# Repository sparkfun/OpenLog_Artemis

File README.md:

SparkFun OpenLog Artemis
===========================================================

<table class="table table-hover table-striped table-bordered">
  <tr align="center">
   <td></td>
   <td></td>
  </tr>
  <tr align="center">
    <td><a href="https://www.sparkfun.com/products/16832">SparkFun OpenLog Artemis (DEV-16832)</a></td>
    <td><a href="https://www.sparkfun.com/products/15846">SparkX OpenLog Artemis (SPX-15846)</a></td>
  </tr>
</table>

The OpenLog Artemis is an open source datalogger that comes preprogrammed to automatically log IMU, GPS, serial data, and various pressure, humidity, and distance sensors. All without writing a single line of code! OLA automatically detects, configures, and logs Qwiic sensors. OLA is designed for users who just need to capture a bunch of data to a CSV and get back to their larger project.

Included on every OpenLog Artemis is an IMU for built-in logging of triple axis accelerometer, gyro, and magnetometer. Whereas the original [9DOF Razor](https://www.sparkfun.com/products/14001) used the old MPU-9250, the OpenLog Artemis uses the latest [ICM-20948](https://www.sparkfun.com/products/15335) capable of nearly 1kHz logging of all 9 axis. We then took over a decade of experience with the original [OpenLog](https://www.sparkfun.com/products/13712) and took it much farther. Simply power up OpenLog Artemis and all incoming serial data is automatically recorded to a log file. Baud rates up to 921600bps are supported! Additionally, based on feedback from users we've added an onboard RTC so that all data can be time stamped.

OpenLog Artemis is highly configurable over an easy to use serial interface. Simply plug in a USB C cable and open a terminal at 115200kbps. The logging output is automatically streamed to both the terminal and the microSD. Pressing any key will open the configuration menu.

The OpenLog Artemis automatically scans, detects, configures, and logs various Qwiic sensors plugged into the board (no soldering required!). Currently, auto-detection is supported on the following Qwiic products:

* Any u-blox GPS Modules (Lat/Long, Altitude, Velocity, SIV, Time, Date) such as:
  * [ZED-F9P](https://www.sparkfun.com/products/15136) 1cm High Precision GPS
  * [NEO-M8P-2](https://www.sparkfun.com/products/15005) 2.5cm High Precision GPS
  * [SAM-M8Q](https://www.sparkfun.com/products/15210) 1.5m 72 Channel GPS
  * [ZOE-M8Q](https://www.sparkfun.com/products/15193) 1.5m Compact GPS
  * [NEO-M9N](https://www.sparkfun.com/products/15712) 1.5m GPS
  * [MAX-M10S](https://www.sparkfun.com/products/18037) 1.5m Ultra-Low Power GPS
* [MCP9600 Thermocouple Amplifier](https://www.sparkfun.com/products/16294)
* [NAU7802 Load Cell Amplifier](https://www.sparkfun.com/products/15242)
* [LPS25HB Barometric Pressure Sensor](https://www.sparkfun.com/products/14767)
* [BME280 Humidity and Barometric Pressure Sensor](https://www.sparkfun.com/products/15440)
* [MS5637 Barometric Pressure Sensor](https://www.sparkfun.com/products/14688)
* [MS5837 Depth / Pressure Sensor](https://www.sparkfun.com/products/17709)
* [SDP3X Differential Pressure Sensor](https://www.sparkfun.com/products/17874)
* [MS8607 Pressure Humidity Temperature Sensor](https://www.sparkfun.com/products/16298)
* [MPR0025PA MicroPressure Sensor](https://www.sparkfun.com/products/16476)
* [TMP102 Temperature Sensor] (https://www.sparkfun.com/products/13314)
* [TMP117 High Precision Temperature Sensor](https://www.sparkfun.com/products/15805)
* [AHT20 Humidity and Temperature Sensor](https://www.sparkfun.com/products/16618)
* [SHTC3 Humidity and Temperature Sensor](https://www.sparkfun.com/products/16467)
* [CCS811 Air Quality Sensor](https://www.sparkfun.com/products/14348)
* [SGP30 Air Quality Sensor](https://www.sparkfun.com/products/16531)
* [SGP40 Air Quality Sensor](https://www.sparkfun.com/products/17729)
* [SCD30 CO<sub>2</sub> and Air Quality Sensor](https://www.sparkfun.com/products/15112)
* [SN-GCJA5 Particle Sensor](https://www.sparkfun.com/products/17123)
* [VEML6075 UV Sensor](https://www.sparkfun.com/products/15089)
* [VCNL4040 Proximity Sensor](https://www.sparkfun.com/products/15177)
* [VL53L1X LIDAR Distance Sensor](https://www.sparkfun.com/products/14722)
* [ADS122C04 ADC PT100 Sensor](https://www.sparkfun.com/products/16770)
* [Qwiic Mux](https://www.sparkfun.com/products/16784) allowing for the chaining of up to 64 unique buses!
* [Pulse Oximeter and Heart Rate Sensor](https://www.sparkfun.com/products/15219) (requires exclusive use of pins 32 and 11)
* [ISM330DHCX IMU](https://www.sparkfun.com/products/19764)
* [MMC5983MA Magnetometer](https://www.sparkfun.com/products/19921)
* [KX134 Accelerometer](https://www.sparkfun.com/products/17589)
* [ADS1015 ADC](https://www.sparkfun.com/products/15334)
* [LPS28DFW Barometer](https://www.sparkfun.com/products/21221)
* [VEML7700 Ambient Light Sensor](https://www.sparkfun.com/products/18981)
* [TMP102 Temperature Sensor](https://www.sparkfun.com/sparkfun-digital-temperature-sensor-tmp102-qwiic.html)

Very low power logging is supported. OpenLog Artemis can be configured to take readings at 500 times a second, or as slow as 1 reading every 24 hours. You choose! When there is more than 2 seconds between readings OLA will automatically power down itself and the sensors on the bus resulting in a sleep current of approximately 18uA. This means a normal [2Ah battery](https://www.sparkfun.com/products/13855) will enable logging for more than 4,000 days! OpenLog Artemis has built-in LiPo charging set at 450mA/hr.

New features are constantly being added so we’ve released an easy to use firmware upgrade tool. No need to install Arduino or a bunch of libraries, simply open the [Artemis Firmware Upload GUI](https://github.com/sparkfun/Artemis-Firmware-Upload-GUI), load the latest OLA firmware, and add features to OpenLog Artemis as they come out! Full instructions are available in [UPGRADE.md](UPGRADE.md).

The OLA can be tailored to many different applications and we will be releasing custom versions of the firmware for those too:

* [Latest OLA firmware](https://github.com/sparkfun/OpenLog_Artemis/tree/main/Binaries)
* [Geophone Logger firmware](https://github.com/sparkfun/OpenLog_Artemis_Geophone_Logger) for logging seismic activity
* [GNSS Logger](https://github.com/sparkfun/OpenLog_Artemis_GNSS_Logger) for advanced data logging with the u-blox F9 and M9 GNSS modules including support for RAWX and RELPOSNED

Repository Contents
-------------------

* **/Binaries** - The binary files for the different versions of the OLA firmware.
* **/Firmware** - The main sketch that runs OpenLog Artemis as well as a variety of sketches to test various sensor interfaces and power saving states.
* **/Hardware** - Eagle files.

Documentation
--------------

* **[Hookup Guide](https://learn.sparkfun.com/tutorials/openlog-artemis-hookup-guide)** - hookup guide for the OLA.
* **[UPGRADE.md](./UPGRADE.md)** - contains full instructions on how to upgrade the firmware on the OLA using the [Artemis Firmware Upload GUI](https://github.com/sparkfun/Artemis-Firmware-Upload-GUI).
* **[CONTRIBUTING.md](./CONTRIBUTING.md)** - guidance on how to contribute to this library.
* **[Installing an Arduino Library Guide](https://learn.sparkfun.com/tutorials/installing-an-arduino-library)** - OLA includes a large number of libraries that will need to be installed before compiling will work.
* **[ADDING_SENSORS.md](./ADDING_SENSORS.md)** - contains _abbreviated_ instructions on how to add a new sensor to the OLA firmware. It's more of an aide-memoire really... Sorry about that.
* **[COMPILE_BINARY.md](./COMPILE_BINARY.md)** - contains instructions on how to compile the OLA firmware binary manually using Docker.
* **[SENSOR_UNITS.md](./SENSOR_UNITS.md)** - contains a summary of the units used for each sensor measurement.

Product Versions
----------------
* [DEV-19426](https://www.sparkfun.com/products/19426) - SparkFun OpenLog Artemis without IMU
* [DEV-16832](https://www.sparkfun.com/products/16832) - SparkFun OpenLog Artemis
* [SPX-15846](https://www.sparkfun.com/products/15846) - SparkX OpenLog Artemis

License Information
-------------------

This product is _**open source**_!

Various bits of the code have different licenses applied. Anything SparkFun wrote is beerware; if you see me (or any other SparkFun employee) at the local, and you've found our code helpful, please buy us a round!

Please use, reuse, and modify these files as you see fit. Please maintain attribution to SparkFun Electronics and release anything derivative under the same license.

Distributed as-is; no warranty is given.

- Your friends at SparkFun.

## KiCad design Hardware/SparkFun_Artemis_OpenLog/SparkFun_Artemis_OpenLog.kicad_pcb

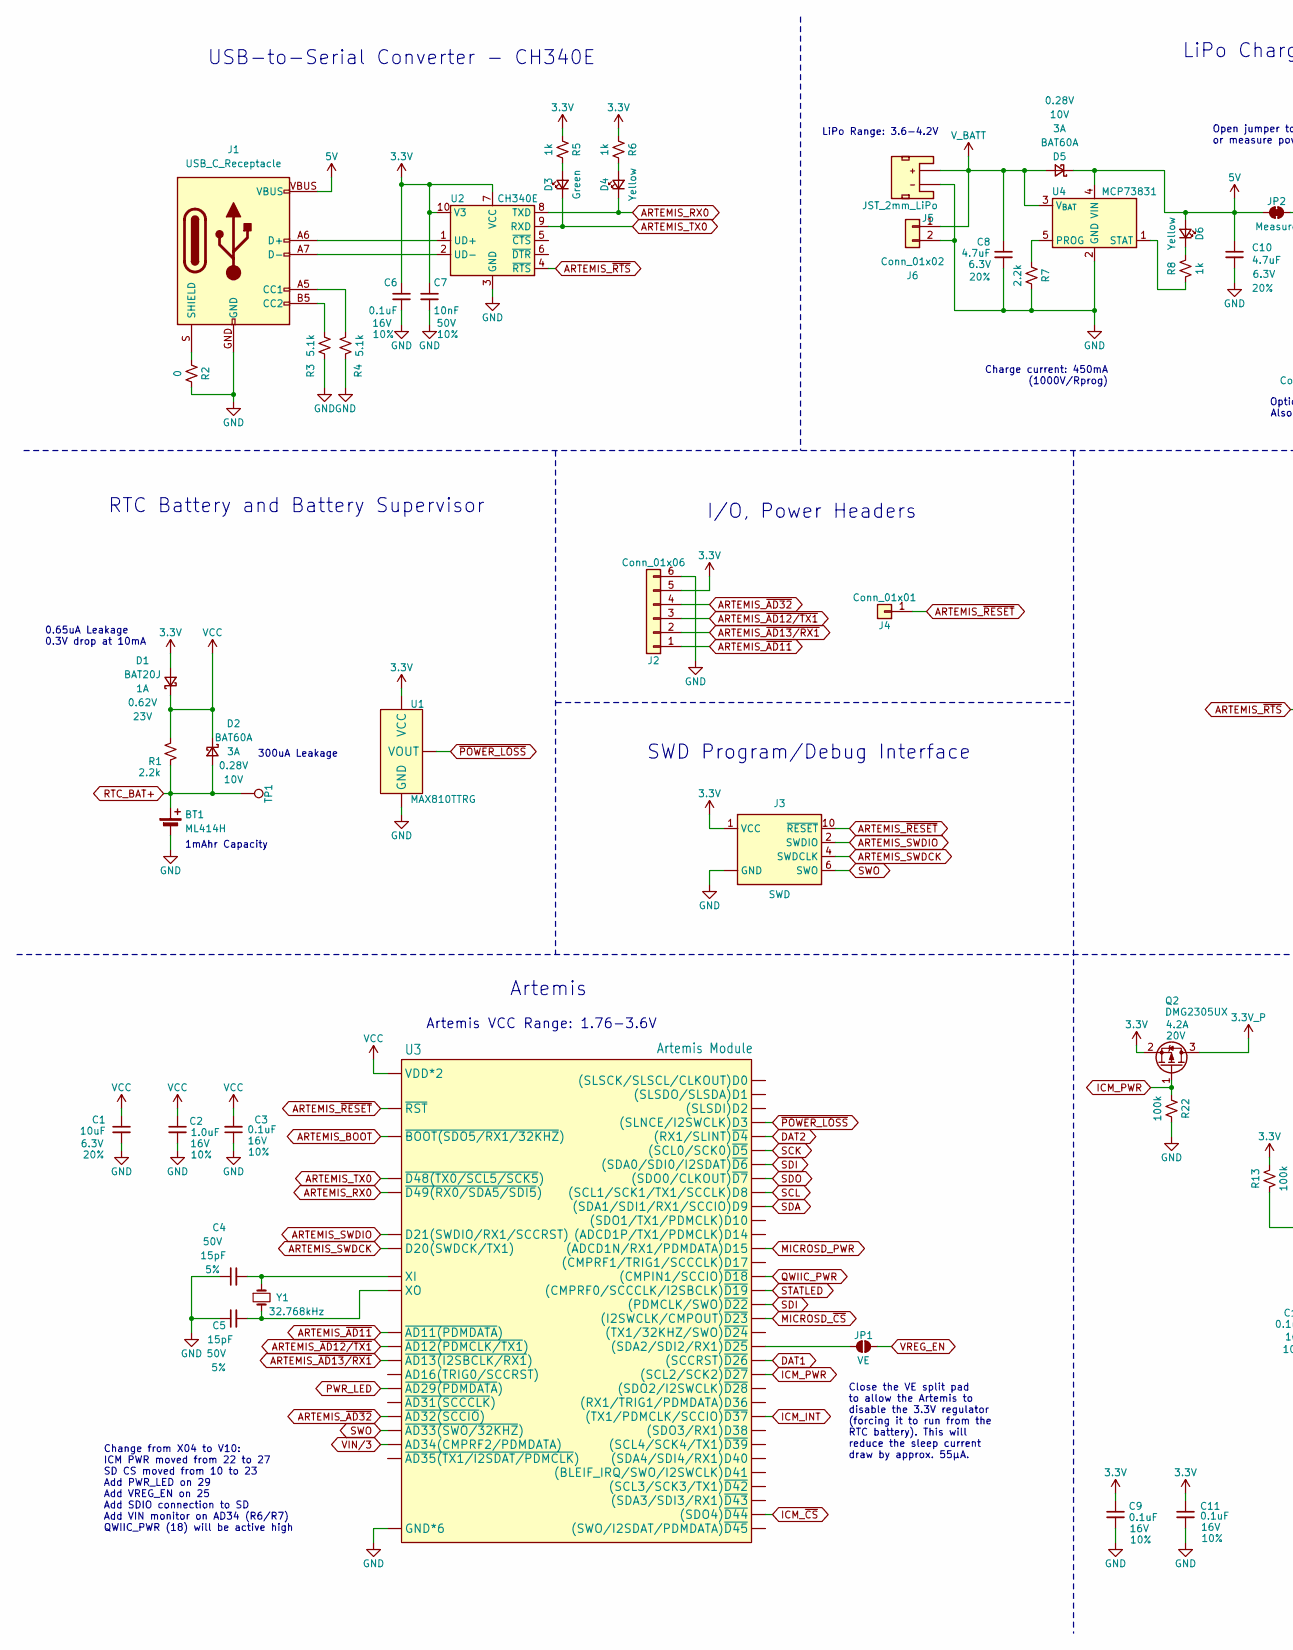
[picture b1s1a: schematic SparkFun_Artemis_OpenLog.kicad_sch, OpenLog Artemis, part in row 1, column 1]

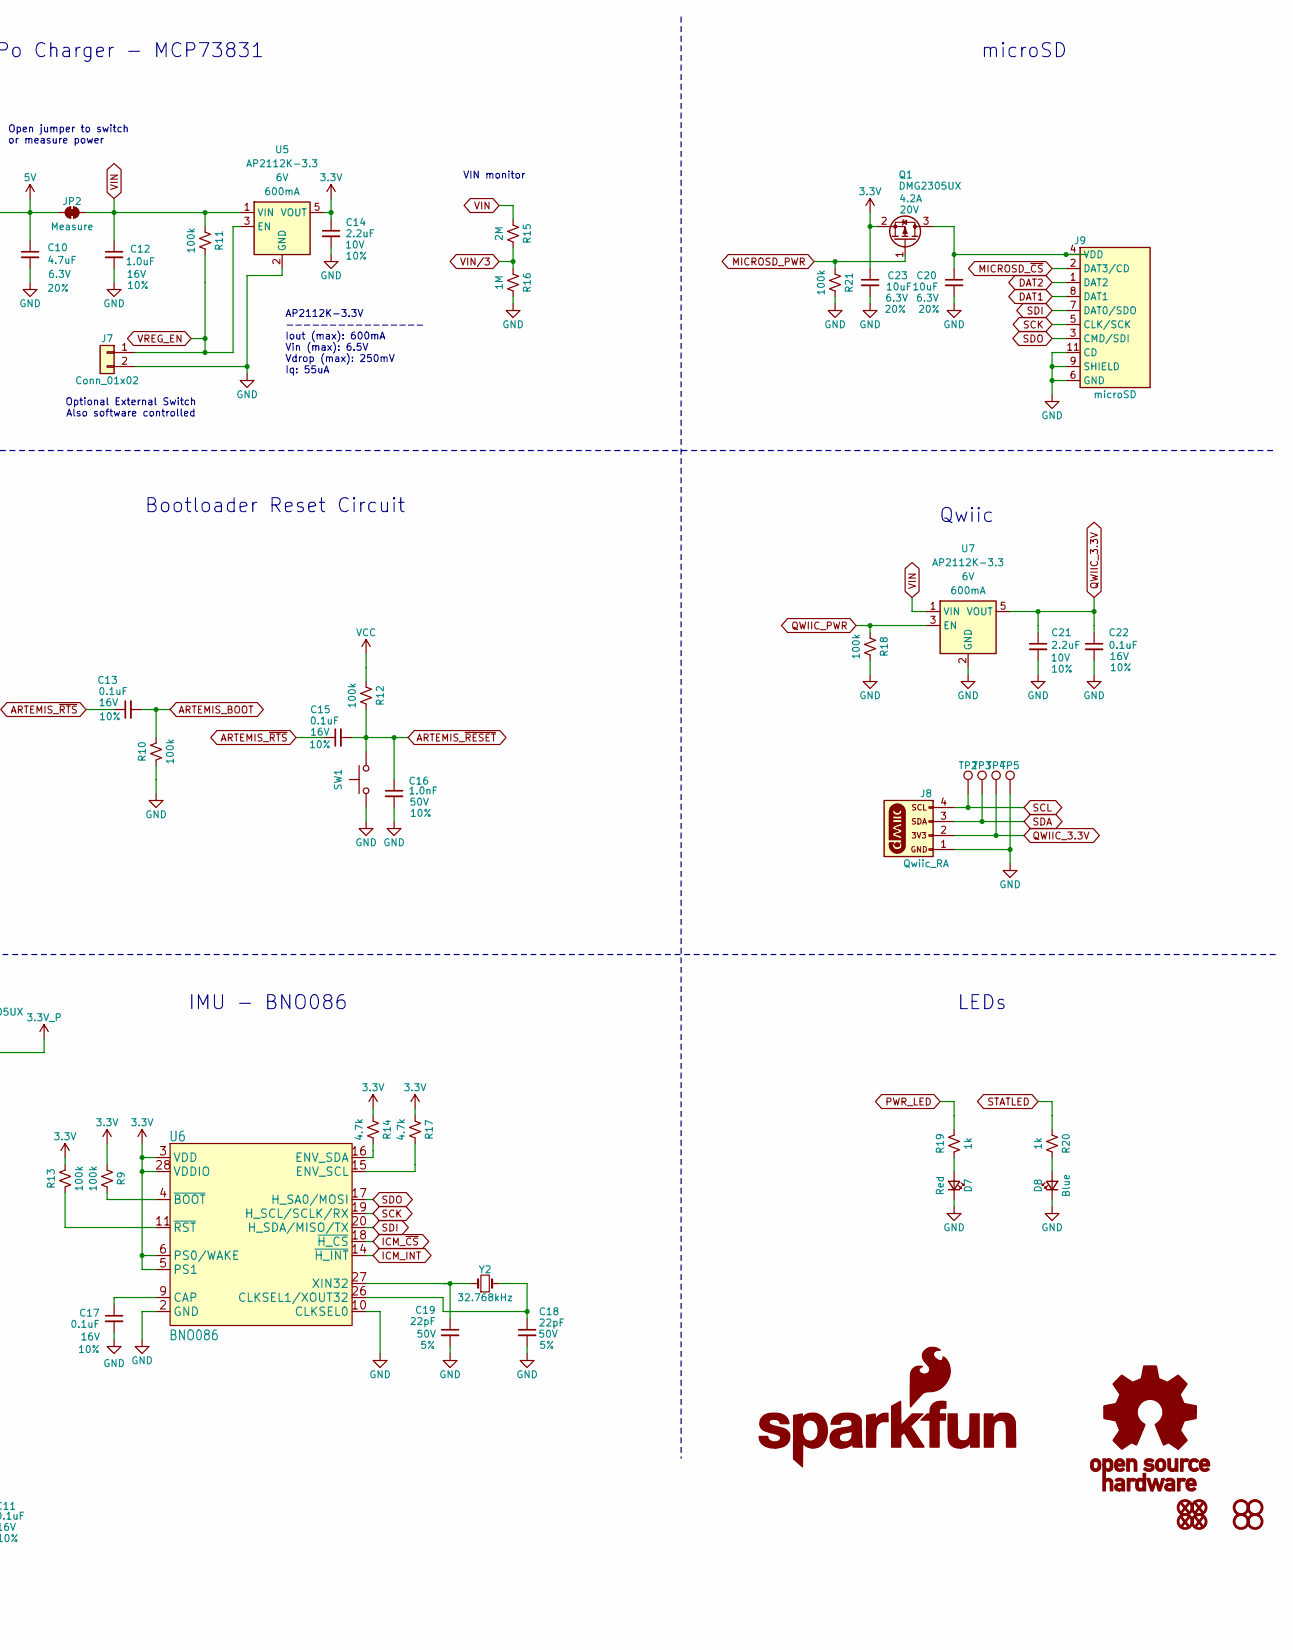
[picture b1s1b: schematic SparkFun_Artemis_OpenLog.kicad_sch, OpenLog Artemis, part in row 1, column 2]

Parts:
BT1: ML414H; ML414H_IV01E
C1, C20, C23: 10uF; C_0402_1005Metric; Voltage 6.3V; Tolerance 20%
C2, C12: 1.0uF; C_0402_1005Metric; Voltage 16V; Tolerance 10%
C3, C6, C9, C11, C13, C15, C17, C22: 0.1uF; C_0402_1005Metric; Voltage 16V; Tolerance 10%
C4, C5: 15pF; C_0402_1005Metric; Voltage 50V; Tolerance 5%
C7: 10nF; C_0402_1005Metric; Voltage 50V; Tolerance 10%
C8, C10: 4.7uF; C_0402_1005Metric; Voltage 6.3V; Tolerance 20%
C14, C21: 2.2uF; C_0402_1005Metric; Voltage 10V; Tolerance 10%
C16: 1.0nF; C_0402_1005Metric; Voltage 50V; Tolerance 10%
C18, C19: 22pF; C_0402_1005Metric; Voltage 50V; Tolerance 5%
D1: BAT20J; SOD-323
D2, D5: BAT60A; SOD-323
D3: Green; LED_0603_1608Metric_Green
D4, D6: Yellow; LED_0603_1608Metric_Yellow
D7: Red; LED_0603_1608Metric_Red
D8: Blue; LED_0603_1608Metric_Blue
FID1, FID2, FID3, FID4: Fiducial_0.5mm; Fiducial_0.5mm_Mask1mm
G1: SparkFun_Logo
G2: OSHW_Logo; Creative_Commons_License
J1: USB_C_Receptacle; USB-C_16
J2: Conn_01x06; 1x06_P2.54mm
J3: SWD; 2x05_P1.27mm
J4: Conn_01x01; 1x01_P2.54mm
J5: JST_2mm_LiPo; JST_1x02_P2.0mm_Horizontal_SMD
J6, J7: Conn_01x02; 1x02_P2.54mm
J8: Qwiic_RA; JST_1x04_P1.0mm_Horizontal_SMD
J9: microSD; microSD_SOCKET
JP1: VE; Jumper_2_NO
JP2: Measure; Jumper_2_PTH_SMD_Combo-NC
Q1, Q2: DMG2305UX; SOT23-3
R1, R7: 2.2k; R_0402_1005Metric
R2: 0; R_0402_1005Metric
R3, R4: 5.1k; R_0402_1005Metric
R5, R6, R8, R19, R20: 1k; R_0402_1005Metric
R9, R10, R11, R12, R13, R18, R21, R22: 100k; R_0402_1005Metric
R14, R17: 4.7k; R_0402_1005Metric
R15: 2M; R_0603_1608Metric
R16: 1M; R_0603_1608Metric
ST1, ST2, ST3, ST4: Standoff
SW1: SMD_4.6x2.8mm_h2.5mm; Push_SMD_4.6x2.8mm_h2.5mm
TP1: 1.0mm; TestPoint-1.0mm
TP2, TP3, TP4, TP5: 0.75mm; TestPoint-0.75mm
U1: MAX810TTRG; SOT23-3
U2: CH340E; MSOP-10_3x3mm_P0.5mm
U3: Artemis Module; Artemis_Module
U4: MCP73831; SOT23-5
U5, U7: AP2112K-3.3; SOT23-5
U6: BNO086; LGA-28_5.2x3.8mm_P0.5mm
Y1, Y2: 32.768kHz; Crystal_SMD_3.2x1.5mm

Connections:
3.3V: C6.1, C7.1, C9.1, C11.1, C14.1, C23.1, D1.2 (A), J2.5, J3.1 (VCC), Q1.2 (S), Q2.2 (S), R5.2, R6.2, R9.2, R13.2, R14.2, R17.2, U1.3 (VCC), U2.7 (VCC), U2.10 (V3), U5.5 (VOUT), U6.3 (VDD), U6.5 (PS1), U6.6 (PS0/WAKE), U6.28 (VDDIO)
5V: C10.1, D5.1 (K), D6.2 (A), J1.VBUS, JP2.1 (A), U4.4 (VIN)
ARTEMIS_BOOT: C13.2, R10.2, U3.BOOT (~BOOT(SDO5/RX1/32KHZ))
ARTEMIS_RX0: D4.1 (K), U2.8 (TXD), U3.RXI-0 (~D49(RX0/SDA5/SDI5))
ARTEMIS_SWDCK: J3.4 (SWDCLK), U3.SWDCK (D20(SWDCK/TX1))
ARTEMIS_SWDIO: J3.2 (SWDIO), U3.SWDIO (D21(SWDIO/RX1/SCCRST))
ARTEMIS_TX0: D3.1 (K), U2.9 (RXD), U3.TXO-0 (~D48(TX0/SCL5/SCK5))
ARTEMIS_~AD11: J2.1, U3.~AD11 (~AD11(PDMDATA))
ARTEMIS_~AD12/TX1: J2.3, U3.~AD12 (~AD12(PDMCLK/TX1))
ARTEMIS_~AD13/RX1: J2.2, U3.~AD13 (~AD13(I2SBCLK/RX1))
ARTEMIS_~AD32: J2.4, U3.~AD32 (~AD32(SCCIO))
ARTEMIS_~RESET: C15.2, C16.1, J3.10 (~RESET), J4.1 (Pin_1_1), R12.1, SW1.2, U3.~RST (~RST)
ARTEMIS_~RTS: C13.1, C15.1, U2.4 (~RTS)
DAT1: J9.8 (DAT1), U3.~D26 ((SCCRST)~D26)
DAT2: J9.1 (DAT2), U3.~D4 ((RX1/SLINT)~D4)
GND: BT1.-, C1.2, C2.2, C3.1, C4.1, C5.1, C6.2, C7.2, C8.2, C9.2, C10.2, C11.2, C12.2, C14.2, C16.2, C17.2, C18.2, C19.2, C20.2, C21.2, C22.2, C23.2, D7.1 (K), D8.1 (K), J1.GND, J2.6, J3.3 (GND), J3.5 (GND), J3.9 (GND), J5.1 (-), J6.2, J7.2, J8.1, J9.6 (GND), J9.9 (SHIELD), J9.10 (GND), J9.11 (CD), J9.12 (CD), R2.1, R3.1, R4.1, R7.1, R10.1, R16.1, R18.1, R21.1, R22.1, SW1.1, TP5.1 (1_1), U1.1 (GND), U2.3 (GND), U3.GND@1 (GND*6), U3.GND@22 (GND*6), U3.GND@38 (GND*6), U3.GND@39 (GND*6), U3.GND@47 (GND*6), U3.GND@59 (GND*6), U4.2 (GND), U5.2 (GND), U6.2 (GND), U6.10 (CLKSEL0), U6.25 (GNDIO), U7.2 (GND)
ICM_INT: U3.~D37 ((TX1/PDMCLK/SCCIO)~D37), U6.14 (~H_INT)
ICM_PWR: Q2.1 (G), R22.2, U3.~D27 ((SCL2/SCK2)~D27)
ICM_~CS: U3.~D44 ((SDO4)~D44), U6.18 (~H_CS)
MICROSD_PWR: Q1.1 (G), R21.2, U3.D15 ((ADCD1N/RX1/PDMDATA)D15)
MICROSD_~CS: J9.2 (DAT3/CD), U3.~D23 ((I2SWCLK/CMPOUT)~D23)
unnamed: C4.2, U3.XI, Y1.1
unnamed: C5.2, U3.XO, Y1.2
unnamed: D3.2 (A), R5.1
unnamed: D4.2 (A), R6.1
unnamed: D6.1 (K), R8.2
unnamed: D7.2 (A), R19.1
unnamed: D8.2 (A), R20.1
unnamed: J1.A5 (CC1), R4.2
unnamed: J1.B5 (CC2), R3.2
unnamed: J1.S (SHIELD), R2.2
unnamed: C20.1, J9.4 (VDD), Q1.3 (D)
unnamed: JP1.1 (A), U3.~D25 ((SDA2/SDI2/RX1)~D25)
unnamed: J1.A6 (D+), J1.B6 (D+), U2.1 (UD+)
unnamed: J1.A7 (D-), J1.B7 (D-), U2.2 (UD-)
unnamed: R7.2, U4.5 (PROG)
unnamed: R8.1, U4.1 (STAT)
unnamed: C17.1, U6.9 (CAP)
unnamed: R17.1, U6.15 (ENV_SCL)
unnamed: R14.1, U6.16 (ENV_SDA)
unnamed: R9.1, U6.4 (~BOOT)
PWR_LED: R19.2, U3.~AD29 (~AD29(PDMDATA))
QWIIC_3.3V: C21.1, C22.1, J8.2, TP4.1 (1_1), U7.5 (VOUT)
QWIIC_PWR: R18.2, U3.~D18 ((CMPIN1/SCCIO)~D18), U7.3 (EN)
RTC_BAT+: BT1.+, D2.2 (A), R1.1, TP1.1 (1_1)
SCK: J9.5 (CLK/SCK), U3.~D5 ((SCL0/SCK0)~D5), U6.19 (H_SCL/SCLK/RX)
SCL: J8.4, TP2.1 (1_1), U3.D8 ((SCL1/SCK1/TX1/SCCLK)D8)
SDA: J8.3, TP3.1 (1_1), U3.D9 ((SDA1/SDI1/RX1/SCCIO)D9)
SDI: J9.7 (DAT0/SDO), U3.~D6 ((SDA0/SDI0/I2SDAT)~D6), U3.~D22 ((PDMCLK/SWO)~D22), U6.20 (H_SDA/MISO/TX)
SDO: J9.3 (CMD/SDI), U3.D7 ((SDO0/CLKOUT)~D7), U6.17 (H_SA0/MOSI)
STATLED: R20.2, U3.~D19 ((CMPRF0/SCCCLK/I2SBCLK)~D19)
SWO: J3.6 (SWO), U3.~AD33/SWO (~AD33(SWO/32KHZ))
VCC: C1.1, C2.1, C3.2, D1.1 (K), D2.1 (K), R1.2, R12.2, U3.VDD@36 (VDD*2), U3.VDD@37 (VDD*2)
VIN: C12.1, JP2.2 (B), R11.2, R15.2, U5.1 (VIN), U7.1 (VIN)
VIN/3: R15.1, R16.2, U3.AD34 (AD34(CMPRF2/PDMDATA))
VREG_EN: J7.1, JP1.2 (B), R11.1, U5.3 (EN)
V_BATT: C8.1, D5.2 (A), J5.2 (+), J6.1, U4.3 (V_{BAT})
~POWER_LOSS: U1.2 (VOUT), U3.D3 ((SLNCE/I2SWCLK)D3)
~RST: R13.1, U6.11 (~RST)

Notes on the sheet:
Charge current: 450mA (1000V/Rprog)
LiPo Charger - MCP73831
USB-to-Serial Converter - CH340E
IMU - BNO086
300uA Leakage
0.65uA Leakage 0.3V drop at 10mA
Optional External Switch Also software controlled
Bootloader Reset Circuit
VIN monitor
RTC Battery and Battery Supervisor
1mAhr Capacity
Close the VE split pad to allow the Artemis to disable the 3.3V regulator (forcing it to run from the RTC battery). This will reduce the sleep current draw by approx. 55μA.
microSD
I/O, Power Headers
Change from X04 to V10: ICM PWR moved from 22 to 27 SD CS moved from 10 to 23 Add PWR_LED on 29 Add VREG_EN on 25 Add SDIO connection to SD Add VIN monitor on AD34 (R6/R7) QWIIC_PWR (18) will be active high
AP2112K-3.3V ---------------- Iout (max): 600mA Vin (max): 6.5V Vdrop (max): 250mV Iq: 55uA
Artemis
LiPo Range: 3.6-4.2V
SWD Program/Debug Interface
Qwiic
Open jumper to switch or measure power
LEDs
Artemis VCC Range: 1.76-3.6V

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
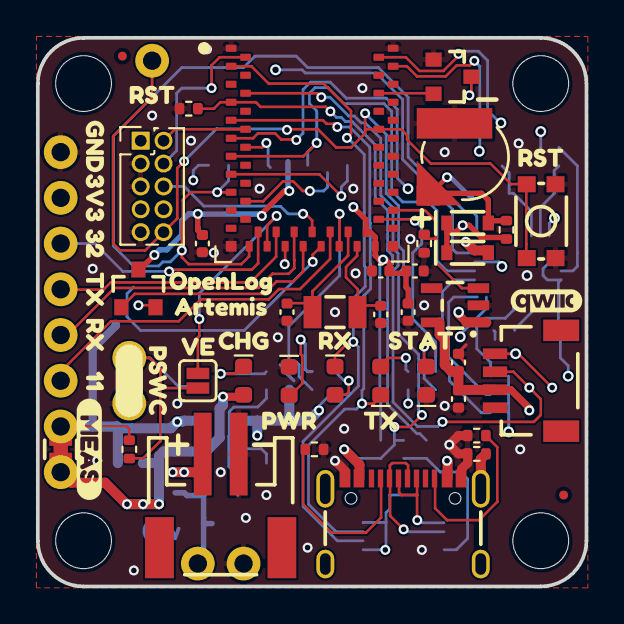
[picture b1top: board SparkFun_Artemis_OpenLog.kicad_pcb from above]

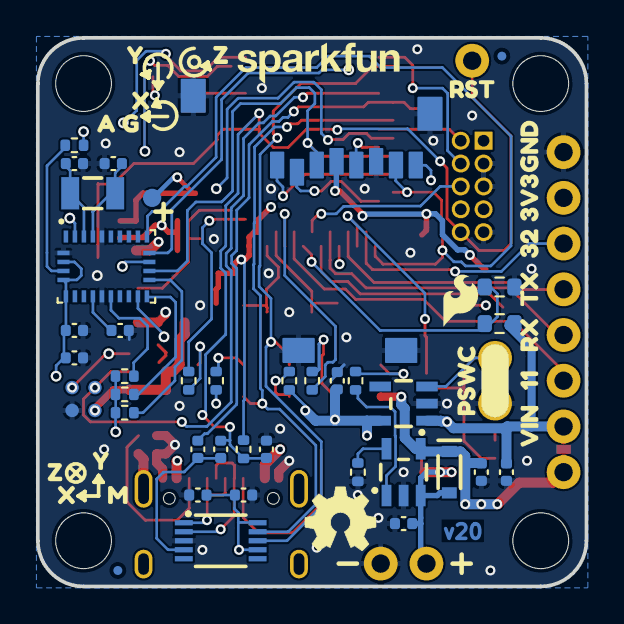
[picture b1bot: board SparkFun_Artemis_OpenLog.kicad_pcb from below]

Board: 4 copper layers, 30.5 x 30.5 mm, 123 parts (63 on the bottom side), 60 nets.

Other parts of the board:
Ref**: Val**; OSHW_Logo_4mm
kibuzzard-6A9865B8: G***; kibuzzard-6A9865B8
kibuzzard-6A9866A0: G***; kibuzzard-6A9866A0
kibuzzard-6A9866A8: G***; kibuzzard-6A9866A8
kibuzzard-6A9866B0: G***; kibuzzard-6A9866B0
kibuzzard-6A9866B9: G***; kibuzzard-6A9866B9
kibuzzard-6A9866BF: G***; kibuzzard-6A9866BF
kibuzzard-6A9866C5: G***; kibuzzard-6A9866C5
kibuzzard-6A9866CC: G***; kibuzzard-6A9866CC
kibuzzard-6A9867BB: G***; kibuzzard-6A9867BB
kibuzzard-6A9867E8: G***; kibuzzard-6A9867E8
kibuzzard-6A9867EE: G***; kibuzzard-6A9867EE
kibuzzard-6A9867F7: G***; kibuzzard-6A9867F7
kibuzzard-6A9868B3: G***; kibuzzard-6A9868B3
kibuzzard-6A98662E: G***; kibuzzard-6A98662E
kibuzzard-6A98663F: G***; kibuzzard-6A98663F
kibuzzard-6A98664C: G***; kibuzzard-6A98664C
kibuzzard-6A98670C: G***; kibuzzard-6A98670C
kibuzzard-6A98671E: G***; kibuzzard-6A98671E
kibuzzard-6A98675F: G***; kibuzzard-6A98675F
kibuzzard-6A98681E: G***; kibuzzard-6A98681E
kibuzzard-6A98683A: G***; kibuzzard-6A98683A
kibuzzard-6A98685A: G***; kibuzzard-6A98685A
kibuzzard-6A98686C: G***; kibuzzard-6A98686C
kibuzzard-6A98687A: G***; kibuzzard-6A98687A
kibuzzard-6A986638: G***; kibuzzard-6A986638
kibuzzard-6A986647: G***; kibuzzard-6A986647
kibuzzard-6A986671: G***; kibuzzard-6A986671
kibuzzard-6A986700: G***; kibuzzard-6A986700
kibuzzard-6A986773: G***; kibuzzard-6A986773
kibuzzard-6A986792: G***; kibuzzard-6A986792
kibuzzard-6A986804: G***; kibuzzard-6A986804
kibuzzard-6A986832: G***; kibuzzard-6A986832
kibuzzard-6A986851: G***; kibuzzard-6A986851
kibuzzard-6A986874: G***; kibuzzard-6A986874
kibuzzard-6A986903: G***; kibuzzard-6A986903

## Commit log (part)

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2020-06-29 V10 PCB tweaks following design review
2020-06-29 Added revised production files (3x5)
2020-06-30 Final V10 PCB tweaks!?
2020-06-30 Corrections and new features for #18
2020-07-04 Added support for the ADS122C04 ADC (Qwiic PT100)
2020-07-14 Reverting to standard SdFat. Removed the wakeOnPowerReconnect & WDT functionality.
2020-07-18 Added the olaIdentifier and corrected the qwiic pull-ups.
    Pull-ups are now only disabled when talking to a u-blox GNSS.
2020-07-18 Removed the last of the msg
2020-07-20 Added qwiicBusPullUps to the settings
2020-07-20 Removing the v14 BETA binaries
2020-07-22 Increase port count to 8 on mux scanner
2020-08-01 Work in progress:
    Added the skeleton of the productionTest however some parts are about to go in the bin as I've just found out that the Apollo3 does not support I2C peripheral mode!
2020-08-01 productionTest now uses the TX and RX pins
2020-08-03 Added the microSD card test
2020-08-03 Changed max serial logging baud rate to 500000.
    Tested serial logging at 460800 and 921600 using u-blox serial data. 460800 works fine but 921600 causes problems... To play safe, I'm limiting the maximum serial logging baud rate to 500000.
2020-08-04 Fixing the slippery mux bug
2020-08-05 Reduce RAM use by making all Serial prints F
2020-08-06 Added EXTRA_MUX_STARTUP_BYTES
2020-08-10 Make I2C scanner work on new v10 hardware. Add delay for devices, ublox needs ~1s to ack.
2020-08-10 Move Qwiic power up delay from startup to detectQwiicDevices()
2020-08-10 Remove erroneous print warning
2020-08-10 Add record length to debug print
2020-08-11 Making board and sch consistant.
2020-08-13 Move up initial power on of Qwiic bus.
    There are a few configurations (no SD card, fast SD card with few files) where OLA powers up the GPS module but fails to detect it because the GPS module needs more time (around 1s) after power on. T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
2020-08-13 Change firmware number
2020-08-13 Whitespace changes - Arduino autoformat
2020-08-13 Add power down before power on for SCD30 test
2020-08-21 Update readme with v10 red OLA
2020-08-21 Update auto-detect list
2020-08-22 Removed duplicated text in README.md
2020-09-01 Added support to output sensor data to the TX pin
2020-09-03 Added file create and access timestamps
2020-09-03 Added measurementTotal
2020-09-04 Added the Tera Term change directory message
2020-09-04 Added qwiic bus power up delays for each sensor type
    Each sensor struct now contains a powerOnDelayMillis.
    qwiicPowerOnDelayMillis is set to the _higher_ of settings.qwiicBusPowerUpDelayMs or the highest power on delay depending on what sensors are attached.
    The minimum value for settings.qwiicBusPowerUpDelayMs is minimumQwiicPowerOnDelay.
2020-09-07 Added frequent log file access timestamps
2020-09-07 Added the ability to trigger a sensor reading via pin 11
2020-09-07 Updated the power-on delay for the SCD30
2020-09-07 Updated the (done) list for v16
2020-09-07 Added the binaries for v16
2020-09-16 Added a fix for issue #39
2020-10-08 Restructuring detectQwiicDevices so that the MCP9600 is detected correctly
2020-10-08 Updating the v17_BETA binary. Now supports the MCP9600.
2020-10-12 Adding support for the MPR MicroPressure and SN-GCJA5 Particle sensors
2020-10-13 Added ADDING_SENSORS.md
2020-10-13 Updated the CHANGELOG and binaries for v1.7
2020-10-14 Updated SENSOR_UNITS.md
2020-10-15 DOP is dimensionless. Who knew!?
2020-11-27 Add logMicroseconds
2020-11-30 Adding support for the BNO080 - ** work in progress ** (does not .begin reliably)
2020-12-01 Revert "Adding support for the BNO080 - ** work in progress ** (does not .begin reliably)"
    This reverts commit cdaf6afa03d717202459b980fb657dd0dfe09e62.
2020-12-06 Changing the sprintf for micros() from %d to %lu
2020-12-06 Adding v19 BETA
2020-12-06 Correcting the magnetometer typo
2021-01-04 goToSleep() is now called with argument
    The goToSleep function is now called with an argument msToSleep so it can be used either when sleeping between samples, or for a potentially much longer sleep when triggered on an external pin.
2021-01-06 Changed minimum Deep Sleep time to global constant
2021-01-06 Added timestamping to Serial data after a newline
2021-01-28 cleanup
2021-01-29 Adding the timestamp feature as described in PR #70 and Issue #63. Deleted settings.getRTCfromGPS
2021-01-29 Adding "sleep on pin" and "wake at specified time" functionality
    These changes are based on code by @ryanneve in PR #64 and suggestions in Issue #46
2021-01-30 Correcting logHertz. Slow logging start and end times now entered as hour and minute - not minute-of-day.
2021-01-30 Adjust msToSleep if checkSleepOnRTCTime is true and we need to wake before slowLoggingIntervalSeconds * 1000
2021-01-30 Update OpenLog_Artemis-V10-v19_BETA.bin
    v1.9 BETA now includes msToSleep adjustment for the RTC case
2021-02-01 Try to stagger SCD30 readings to stagger the peak current draw
2021-02-02 Adding resetOnZeroDeviceCount
2021-02-02 Re-adding BNO080
2021-02-02 Adding SGP40, SDP3X and MS5837
2021-02-05 Improvements for the MS5837
2021-02-28 Adding IMU DMP examples
2021-03-09 SDP3X corrections - need to use continuous measurements
2021-03-09 Adding stopContinuousMeasurement for the SDP3X
2021-03-10 SDP3X: add 1ms delay between stopContinuousMeasurement and startContinuousMeasurement
2021-03-30 Correct issue #79
2021-03-30 Update low-power code as per #78
2021-03-30 Update DMP examples
2021-04-23 Correct Issue #82
2021-04-26 Add IMU DMP Multiple Sensors example - requires v1.2.5 of the ICM20948 library
2021-04-26 Initial commit with DMP support
2021-05-28 Add support for exFAT. Requires v2.0.6 of Bill Greiman's SdFat library
2021-05-28 Add minimumAwakeTimeMillis : #83
2021-05-28 minimumAwakeTimeMillis improvements. Fix an old bug in msBeenAwake
2021-05-30 Update to Apollo3 v2.1.0 - work in progress
2021-05-31 Adding oximeter MODE_TWO support
2021-06-01 Update GNSS_Data_Logging.ino - add exFAT support (SdFat v2.0.6)
2021-06-04 Add printf support
2021-06-18 Debugging sleep functionality
2021-07-05 Increase DMP data to five decimal places
2021-07-05 Add v1.12 BETA binary
2021-07-07 Fix goToSleep. Increase DMP resolution. Add bestMillis(). Add comma after olaftoa values.
    With v2.1 of the core, both millis and micros are corrupted when coming out of deep sleep. bestMillis will use the RTC to generate the milliseconds.
2021-07-08 Add configureSerial1TxRx. Improvements to the sleep current - disable SPI and qwiic pins.
2021-07-09 Add printGNSSDebugMessages and gnssFactoryDefault
2021-07-15 Corrections for Qwiic bus speed (100kHz and 400kHz). Ensure interrupt directions are set correctly.
2021-07-16 v2.0
2021-08-17 Update test sketches for v2.1 of Apollo3
2021-08-17 Update AutoDetectWithMux - add ICM20948
2021-09-11 Simplify SD_FAT_TYPE type switching
2021-09-11 Update gitignore
2021-12-14 Add BME280 test to correct issue #109
2021-12-14 Update change notes
2022-03-31 Add support for yyyy/mm/dd and ISO 8601 date. Add fix for Serial.end.
    Add support for missing / not-populated IMU.
    Note: we're not out of the woods yet... The IMU is not restarting after sleep. More changes to follow!
2022-03-31 Add support for fractional time zone offsets
2022-04-01 Use rtcMillis everywhere
2022-04-07 Correct ublox spelling. Update production test. Add X04 BETA binary.
2022-04-08 Release firmware 2.2
2022-05-02 Update OpenLog_Artemis.ino
    Only go into menu on character ASCII value >= 11. Prevents menu if qwiic powered BLE module generates noise on power-up.
2022-08-01 v1.2.3
2022-08-01 v2.3
2022-08-16 Add NoPowerLossProtection option and binary
2022-08-18 minor refactor of header output logic, added header output token for serial output, removed print of header to serial on file change, moved strcat to strlcat
2022-08-26 Add settings.openMenuWithPrintable - accessible from the "d" debug menu
2022-09-06 Update README.md
    Request by a customer to add the recently released MAX-M10S to the list of GNSS modules. I also updated the wording to indicate that the OpenLog Artemis can be linked to any of the u-blox modules.
    No need to update the version number of this repo since it's just the README.md .
2022-12-02 Add support for BMP390 on 0x77
2022-12-05 Set sampling mode to normal precision
2022-12-05 Fix mistakes preventing compiling and adding readme files
2023-01-10 Adds SD card menu timeout (60 sec)
2023-01-10 Re-use same datafile after entering SD card menu unless deleted
2023-01-12 Add debug menu set options for nextDataLogNumber and nextSerialLogNumber
2023-01-12 Correct MMC5983 scaling
2023-01-13 Undo log file reset feature
2023-01-13 ISM330 improvements
2023-01-13 Resolve #87
2023-01-13 Update version comments
2023-01-18 Update 2.5 binaries - correct KX134 functionality
2023-01-23 Add support for ICM20948 via I2C
    Acceleration, Gyro, Mag and Temp supported.
2023-02-06 Only disable I2C SDA and SCL during sleep when I2C bus is being powered down.
2023-02-28 Add input buffer flush on wakeup from sleep
2023-03-28 Added scripts to build using arduino-cli.
2023-03-28 add support for INA3221, MCP23017 and MAX11615
2023-08-29 add a dockerfile for compiling the firmware
2023-08-30 install unzip at start
2023-08-30 don't install unnecessary packages
2023-08-30 Add LPS28DFW library
2023-09-14 docker: cache build
2023-09-18 downgrade sdfat to 2.2.0
2023-10-25 Added SCD30 FRC calibration to config menu
2023-10-25 Corrected original ICM20948 path, whitespace
2024-02-21 Add missing quote
2024-02-21 Enable DMP with sed
2024-02-21 Pushing new firmware binary
2024-02-21 Tidy up after #179
2024-02-21 Update comments
2024-02-21 Allow negative weights on NAU7802
2024-02-22 Fix nvm calibrationWeight
2024-02-22 NAU7802 improvements - skip calibrateAFE on begin
2024-02-24 Better NAU7802 support - needs v1.0.5 of the NAU7802 library
2024-02-26 Change zeroOffset type
2024-02-26 Fix minor bug : pass correct array size to olaftoa
2024-02-26 Fix major bug : configure Mux when changing settings of NAU7802, SCD30 or u-blox GNSS
2024-03-04 2.7 BETA
2024-03-07 v2.8 BETA - to resolve #192
2024-03-07 v2.8 BETA
2024-08-09 Update version notes
2024-09-13 Adding TMP102 library link to documentation as a required library.
2024-09-14 Updated documentation to reflect the new package path name.
2024-09-22 Added support for differentating between the ADS1015 ADC chip vs the TMP102 temperature sensor based upon the R0/R1 configuration bits in the TMP102 which are locked read only to 11, while the same b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
2024-11-08 Revert SparkFun_ICM-20948_ArduinoLibrary vs SparkFun_ICM-20948_ArduinoLibrary
2024-11-08 Moving "(done)" comment to bottom of list
2024-11-11 Add TMP102 to build actions
2025-02-03 actions/upload-artifact@v4
2025-02-06 Where possible, write residual serial data to file before closing
2025-02-06 Don't delete OLA_ settings.txt
2025-02-06 Update sdCardHelp
2025-09-17 Add Mode 1/2 option for LPS28DFW sensor with SD card persistence
2025-11-07 Move LPS28DFW setModeConfig into configureDevice
2025-11-07 v2.11
2025-11-07 Update Dockerfile - comment power loss protection and X04 build

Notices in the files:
parts and their libraries:
Released under the Creative Commons Attribution Share-Alike 4.0 License
https://creativecommons.org/licenses/by-sa/4.0
